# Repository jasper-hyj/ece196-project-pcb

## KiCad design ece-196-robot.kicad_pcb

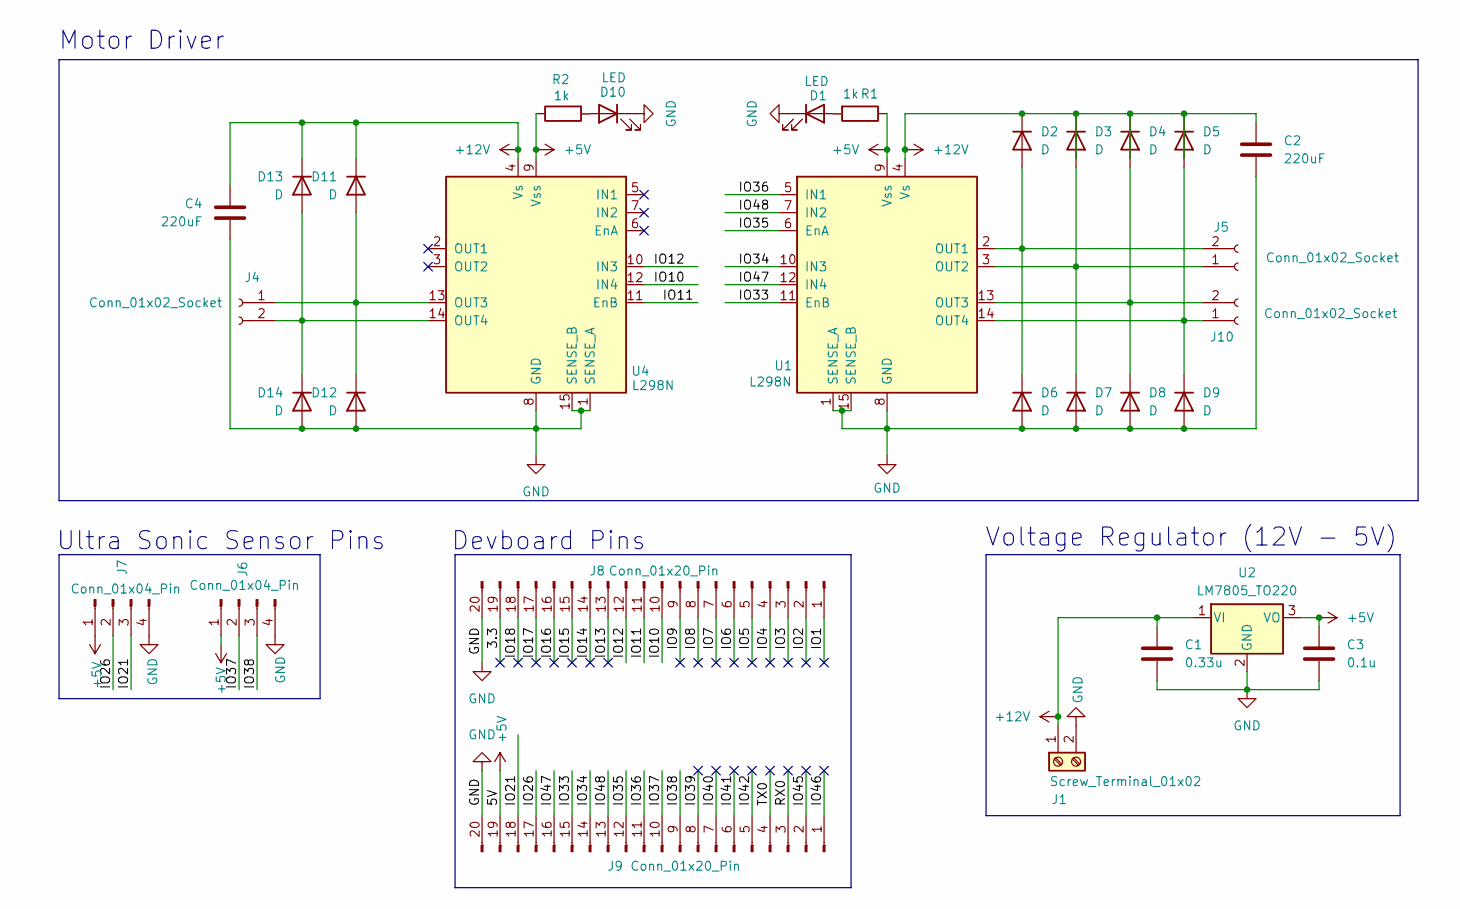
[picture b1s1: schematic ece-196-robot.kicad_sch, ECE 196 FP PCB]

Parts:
C1: 0.33u; C_1206_3216Metric_Pad1.33x1.80mm_HandSolder
C2, C4: 220uF; C_Elec_8x10.2
C3: 0.1u; C_1206_3216Metric_Pad1.33x1.80mm_HandSolder
D1, D10: LED; LED_0805_2012Metric_Pad1.15x1.40mm_HandSolder
D2, D3, D4, D5, D6, D7, D8, D9, D11, D12, D13, D14: D; D_0805_2012Metric_Pad1.15x1.40mm_HandSolder
J1: Screw_Terminal_01x02; TE_282837-2
J4, J5, J10: Conn_01x02_Socket; PinSocket_1x02_P2.54mm_Vertical
J6, J7: Conn_01x04_Pin; PinSocket_1x04_P2.54mm_Vertical
J8, J9: Conn_01x20_Pin; PinSocket_1x20_P2.54mm_Vertical
R1, R2: 1k; R_0805_2012Metric_Pad1.20x1.40mm_HandSolder
U1, U4: L298N; TO-220-15_P2.54x5.08mm_StaggerOdd_Lead4.58mm_Vertical
U2: LM7805_TO220; TO-220-3_Vertical

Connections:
+5V: C3.1, J6.1, J7.1, J9.19, R1.1, R2.1, U1.9 (Vss), U2.3 (VO), U4.9 (Vss)
+12V: C1.1, C2.1, C4.1, D2.1 (K), D3.1 (K), D4.1 (K), D5.1 (K), D11.1 (K), D13.1 (K), J1.1, U1.4 (Vs), U2.1 (VI), U4.4 (Vs)
/3.3: J8.19
/IO1: J8.1
/IO2: J8.2
/IO3: J8.3
/IO4: J8.4
/IO5: J8.5
/IO6: J8.6
/IO7: J8.7
/IO8: J8.8
/IO9: J8.9
/IO10: J8.10, U4.12 (IN4)
/IO11: J8.11, U4.11 (EnB)
/IO12: J8.12, U4.10 (IN3)
/IO13: J8.13
/IO14: J8.14
/IO15: J8.15
/IO16: J8.16
/IO17: J8.17
/IO18: J8.18
/IO21: J7.3, J9.18
/IO26: J7.2, J9.17
/IO33: J9.15, U1.11 (EnB)
/IO34: J9.14, U1.10 (IN3)
/IO35: J9.12, U1.6 (EnA)
/IO36: J9.11, U1.5 (IN1)
/IO37: J6.2, J9.10
/IO38: J6.3, J9.9
/IO39: J9.8
/IO40: J9.7
/IO41: J9.6
/IO42: J9.5
/IO45: J9.2
/IO46: J9.1
/IO47: J9.16, U1.12 (IN4)
/IO48: J9.13, U1.7 (IN2)
/RX0: J9.3
/TX0: J9.4
GND: C1.2, C2.2, C3.2, C4.2, D1.1 (K), D6.2 (A), D7.2 (A), D8.2 (A), D9.2 (A), D10.1 (K), D12.2 (A), D14.2 (A), J1.2, J6.4, J7.4, J8.20, J9.20, U1.1 (SENSE_A), U1.8 (GND), U1.15 (SENSE_B), U2.2 (GND), U4.1 (SENSE_A), U4.8 (GND), U4.15 (SENSE_B)
unnamed: D1.2 (A), R1.2
unnamed: D2.2 (A), D6.1 (K), J5.2, U1.2 (OUT1)
unnamed: D3.2 (A), D7.1 (K), J5.1, U1.3 (OUT2)
unnamed: D4.2 (A), D8.1 (K), J10.2, U1.13 (OUT3)
unnamed: D5.2 (A), D9.1 (K), J10.1, U1.14 (OUT4)
unnamed: D10.2 (A), R2.2
unnamed: D11.2 (A), D12.1 (K), J4.1, U4.13 (OUT3)
unnamed: D13.2 (A), D14.1 (K), J4.2, U4.14 (OUT4)

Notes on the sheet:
Devboard Pins
Voltage Regulator (12V - 5V)
Motor Driver
Ultra Sonic Sensor Pins

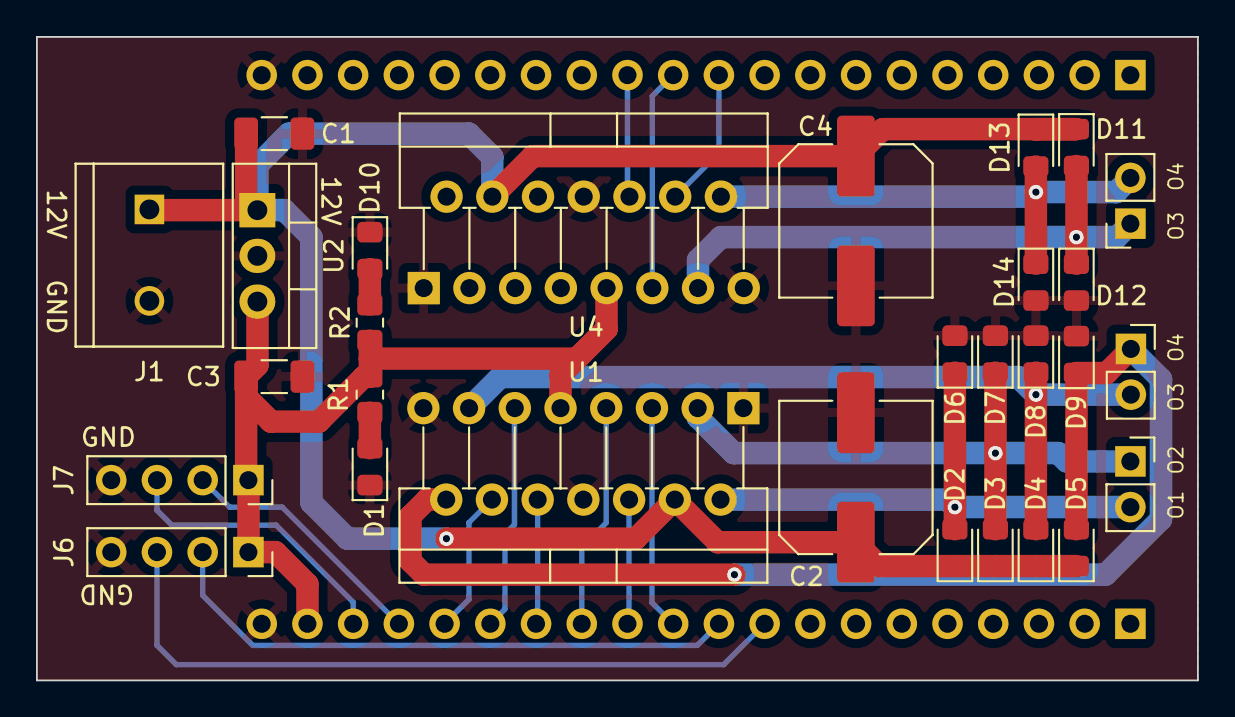
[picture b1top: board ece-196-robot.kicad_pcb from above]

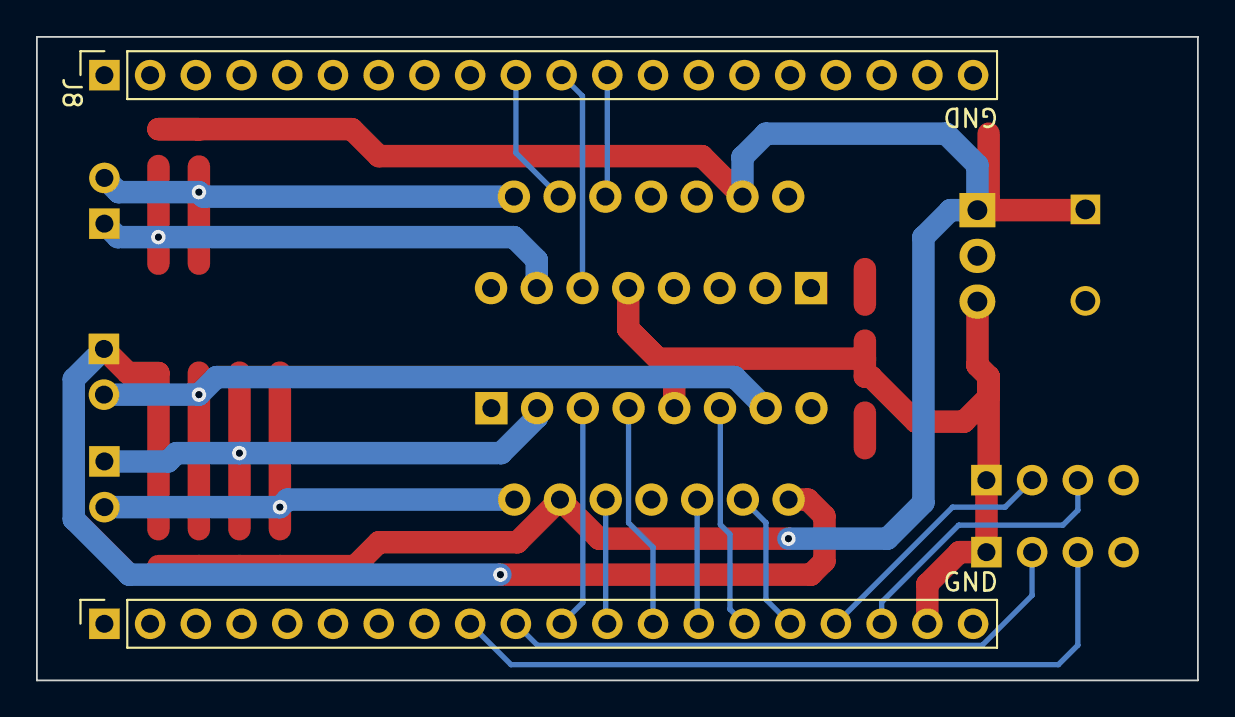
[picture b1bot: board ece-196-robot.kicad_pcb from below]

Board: 2 copper layers, 64.5 x 35.8 mm, 31 parts (2 on the bottom side), 24 nets.

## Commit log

2025-05-14 Update PCB schematic
2025-05-14 Update board
